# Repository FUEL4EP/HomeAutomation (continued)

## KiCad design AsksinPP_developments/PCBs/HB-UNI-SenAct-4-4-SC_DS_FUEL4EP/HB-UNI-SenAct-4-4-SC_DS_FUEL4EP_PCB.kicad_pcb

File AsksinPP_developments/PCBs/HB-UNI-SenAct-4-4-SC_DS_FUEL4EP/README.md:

# HB-UNI-SenAct-4-4-SC_DS_FUEL4EP   

**Platine für DIY AsksinPP für**
- 3x Schaltaktor für Betrieb an einem Netzfreischalter
- Akkubetrieb im Standby, automatische Ladeschaltung
- bei Aktivierung eines Aktors wird die Netzspannung zugeschaltet und am Ende wieder abgeschaltet

- geringer Standby-Verbrauch von ca. 1 mA @ 5V Vaccu, an einer weiteren Reduktion wird gearbeitet
- ein handelsübliches [4 Kanal Relais Modul](https://www.ebay.de/itm/155095219126) wird mit Distanzhaltern "huckepack" auf die Basisplatine montiert
	+ bitte darauf achten, dass das Relais-Modul den Aufdruck [P2H1588A0](./PNGs/4-Relais Modul_top_view.png) hat, da Module mit unterschiedlichen Maßen im Handel verfügbar sind.
	+ die Außenmaße des Relais-Moduls sollten 72,2 mm x 52 mm betragen
- ein STL-Modell eines 3D-druckbaren Gehäuses wird mitgeliefert, die Außenmaße des gedruckten Gehäuses sind 20,8 cm (Breite) x 13,3 cm (Tiefe) x 6,8 cm /(Höhe).
- 3x Einbausteckdosen 45 mm x 45 mm, z.B. DELOCK 81321 Easy 45 Schutzkontakt-Steckdose, werden an der Rückseite des Gehäuses angebracht
- **diese Schaltung und Platine darf ausschließlich von ausgebildeten elektrischen Fachkräften verwendet werden, siehe Disclaimer unten!**
- als passende Sketche stehen zur Verfügung:
	+ [HB-UNI-SenAct-4-4-SC_DS.ino](../../sketches/HB-UNI-SenAct-4-4-SC_DS/)
		* Abfrage der Gerätetasten durch 'Polling'
	+ [HB-UNI-SenAct-4-4-RC_DS.ino](../../sketches/HB-UNI-SenAct-4-4-RC_DS/)
		* Gerätetasten lösen einen Interrupt aus
	- Fragen und Rückmeldungen per PN bei [FUEL4EP](https://homematic-forum.de/forum/ucp.php?i=pm&mode=compose&u=20685) im Homematic Forum nachfragen.
- die Platine V1.5 behebt Fehler, die bei der Validierung eines Prototypen festgestellt und korrigiert wurden. Bitte **keine** Platinen der Versionen V1.0 bis V1.4 verwenden.
- ein passendes 3D-druckbares Gehäuse ist im STL Format und openSCAD Format [hier](./3D_Printer/case/) zu finden

	+ ein 3D Druck wurde damit erfolgreich durchgeführt, ein Prototyp ist erfolgreich aufgebaut und weitgehend validiert worden, siehe entsprechende Bilder im Verzeichnis [PNGs](./PNGs)
- **wichtige Aufbauhinweise:**
- die Materiallisten sind unter [BOM](./BOM) zu finden
    + zuerst die Niederspannungsplatine HB-UNI-SenAct-4-4-SC_DS_FUEL4EP_PCB Schritt für Schritt aufbauen, in Betrieb nehmen und testen:
	    * der Schaltplan der Platine ist [hier](./schematics/HB-UNI-SenAct-4-4-SC_DS_FUEL4EP_PCB.pdf) oder in der bereitgestellten KiCAD-Datenbasis
        + für den Arduino Pro Mini und den CC1101 Tranceiver **vor Einbau** in einem externen Testbed den Ruhestrom prüfen (<10uA) und einen Frequenztest durchführen!
        + das 'Huckepack'-4-Kanal-Relaismodul noch nicht anbringen
    - die Ausgangsspannung des Aufwärtsreglers HW-668 **vor dem Einbau** auf 7,3 Volt einstellen. Dabei eine Eingangsspannung von 5 Volt verwenden.
    - das Schaltnetzteil TIW 06-105 mit dem [3D gedruckten Stift im Gehäuseunterteil fixieren](./PNGs/internal_3.png). Vorher die Netzanschlussleitung des Schaltnetzteils auf die benötigte Länge kürzen und abisolieren.
    - das [4-fach AA Batteriefach](https://www.amazon.de/Batteriehalter-Mignon-Akkuhalter-Batteriefach-Schalter-4x-AA/dp/B0761TSC32?th=1) **unbedingt** mit dem Schalter nach [unten](./PNGs/internal_1.png) in das vorgesehene Fach platzieren, sonst werden die Anschlussdrähte beschädigt und es droht ein Kurzschluss der Akkus!
    + die 230V Schaltungsteile erst dann anschließen, wenn der Rest vollständig geprüft wurde und die Software alle notwendigen Funktionen zeigt.
        * als Erstes dann das 'Huckepack'-4-Kanal-Relaismodul anbringen und nur die Steuersignale verbinden, noch keine 230V Spannungen an den Relaisausgängen anschließen
        * dann die Funktion testen
        * falls manche LEDs (z.B. orange, blau oder pinke LEDs) zu hell im Vergleich zu den anderen LEDs leuchten sollten, bitte einen größeren Vorwiderstand wählen, z.B. 4.7 kOhm. Der vergrößerte Vorwiderstand kann auch in die 'fliegende' Vorverdrahtung der Gehäusevorderwand eingelötet werden.
        * pinke LED benötigen einen ca. 10kOhm Vorwiderstand
        * blaue LEDs benötigen einen ca. 4,7kOhm Vorwiderstand
        * erst als Letztes die 230V Verdrahtung mit der gebotenen Vorsicht anbringen
        * den Nullleiter innerhalb des Gehäuses mit einer 5-fach Wago-Klemme WAGO 221-415 (Reichelt) aus fünf Segmenten herstellen, die zwischen Platine und den Einbausteckdosen platziert wird.
        * bitte nicht vergessen, eine Sicherung einzuschrauben
        * alle Netzleitungen mit 1,5 mm2 Leitungen durchführen
        * alle Netzverbindungen spannungsfrei mit einem Ohmmeter auf Korrektheit und Niederohmigkeit prüfen
        * alle Schrauben, vor allem die an den Einbausteckdosen und an den Relaiskontakten, fest anziehen. Nach erfolgtem Aufbau nochmals auf Festigkeit prüfen.
        * die Anschlüsse an die Kaltgerätebuchse löten
        * Einbausteckdosen und Kaltgerätebuchse in die Gehäuserückwand einkleben
        * bitte darauf achten, dass Nullleiter und Phase entsprechend des [Schaltplans](./schematics/HB-UNI-SenAct-4-4-SC_DS_FUEL4EP_case.pdf) angeschlossen werden. Die Phase muss jeweils mit den Relais geschaltet werden. Bitte den Stecker des Kaltgerätekabels so in die Steckdose stecken, dass diese Zuordnung erhalten bleibt. 
        * sollte die blaue LED D1 bei Dunkelheit periodisch leicht glimmen, dann bitte einen 0,5W 220kOhm Widerstand, wie im [Schaltplan](./schematics/HB-UNI-SenAct-4-4-SC_DS_FUEL4EP_case.pdf) des Gehäuses angegeben, einlöten.
        * sollte die blaue LED D1 bei Dunkelheit dauerhaft glimmen, dann bitte einen 0,22uF 250V K X2 Kondensator die blaue LED D1 bei Dunkelheit. Es darf nur ein für 250V geeigneter Entstörkondensator verwendet werden!
        * gegebenenfalls Zugentlastungen für das Netzkabel anbringen!

## Versionen
- KiCad Schaltplan-Editor Version: 8.0.5-8.0.5-0~ubuntu22.04.1, release build unter Kubuntu22.04.1
- KiCad Leiterplatteneditor Version: 8.0.5-8.0.5-0~ubuntu22.04.1, release build unter Kubuntu22.04.1
- PCB Version 1.7 (Migration auf KiCAD 8 am 01. Okt 2024)
- Schematics  1.5 (Migration auf KiCAD 8 am 01. Okt 2024)

## Wichtige Sicherheitshinweise

- bitte die maximale Strombelastbarkeit der Relais beachten, siehe Aufdruck:

- auch bei rein ohmschen Lasten sollte die maximale Strombelastbarkeit der Relais nicht ausgereizt werden.
- bei induktiven Lastanteilen sollte weniger als die Hälfte des spezifizierten Maximalstroms zugrunde gelegt werden.  Bitte lesen Sie dazu das Datenblatt des Relais oder fragen Sie Ihre Elektrofachkraft.
- während einer längeren Abwesenheit sollte der Netzstecker der Geräts gezogen werden
- die Schaltsignale für die Relais sind **nicht** verschlüsselt. Daher bitte eine Lasten anschließen, die eventuell einen Brand auslösen könnten.
- sollte die Homematic/RaspberryMatic-Zentrale  vom Internet aus erreichbar sein, darf dieser Schalter nicht eingesetzt werden! Für die Sicherheit ist der Nutzer alleine verantwortlich!
- die automatische Ladeschaltung ist zur Zeit noch nicht in Software implementiert! Der Nutzer ist für den korrekten Ladezustand der Akkus verantwortlich.
- ein automatische Ladeschaltung wird in Zukunft als Update zur Verfügung gestellt werden. Das kann aber noch eine Weile dauern ..
- der Schalter funktioniert nun seit über einem Jahr auch ohne automatische Ladesoftware bei täglicher Nutzung: Stand Oktober 2024. Das 15 minütige Nachladen beim Einschalten reicht aus, um die Akkus ausreichend geladden zu halten.

## Fernsteuerung der Aktorkanäle mit Apple iPAD

- das Ein- und Ausschalten von Lasten kann z.B. mit Kurzbefehlen (ShortCuts) auf einem Apple iPAD gesteuert werden, siehe [hier](./control_by_iPAD_shortcuts)

## Disclaimer

- aufgrund der im Gerät frei geführten Netzspannung und des Netzspannungsanschlusses darf die Installation nur von Fachkräften durchgeführt werden, die aufgrund ihrer Ausbildung dazu befugt sind.
- die einschlägigen Sicherheits- und VDE-Bestimmungen sind unbedingt zu beachten. Durch eine unsachgemäße Installation können Sach- und Personenschäden verursacht werden, für die der Errichter haftet.
- Installationsarbeiten sowohl am primärseitigen Netzanschluss als auch am Sekundäranschluss dürfen nur **im stromlosen Zustand erfolgen. Dabei sind alle einschlägigen Vorschriften des Installationshandwerks zu beachten!** 
- alle 230 V Spannung führenden Leitungen und Lötanschlüsse sind im spannungslosen Zustand fachgerecht mit Isolationsband vor Berührungen zu schützen
- die Nutzung der hier veröffentlichten Inhalte erfolgt vollständig auf eigenes Risiko und ohne jede Gewähr

## Lizenz 

**Creative Commons BY-NC-SA**<br>
Give Credit, NonCommercial, ShareAlike

<br />This work is licensed under a <a rel="license" href="http://creativecommons.org/licenses/by-nc-sa/4.0/">Creative Commons Attribution-NonCommercial-ShareAlike 4.0 International License</a>.

-EOF

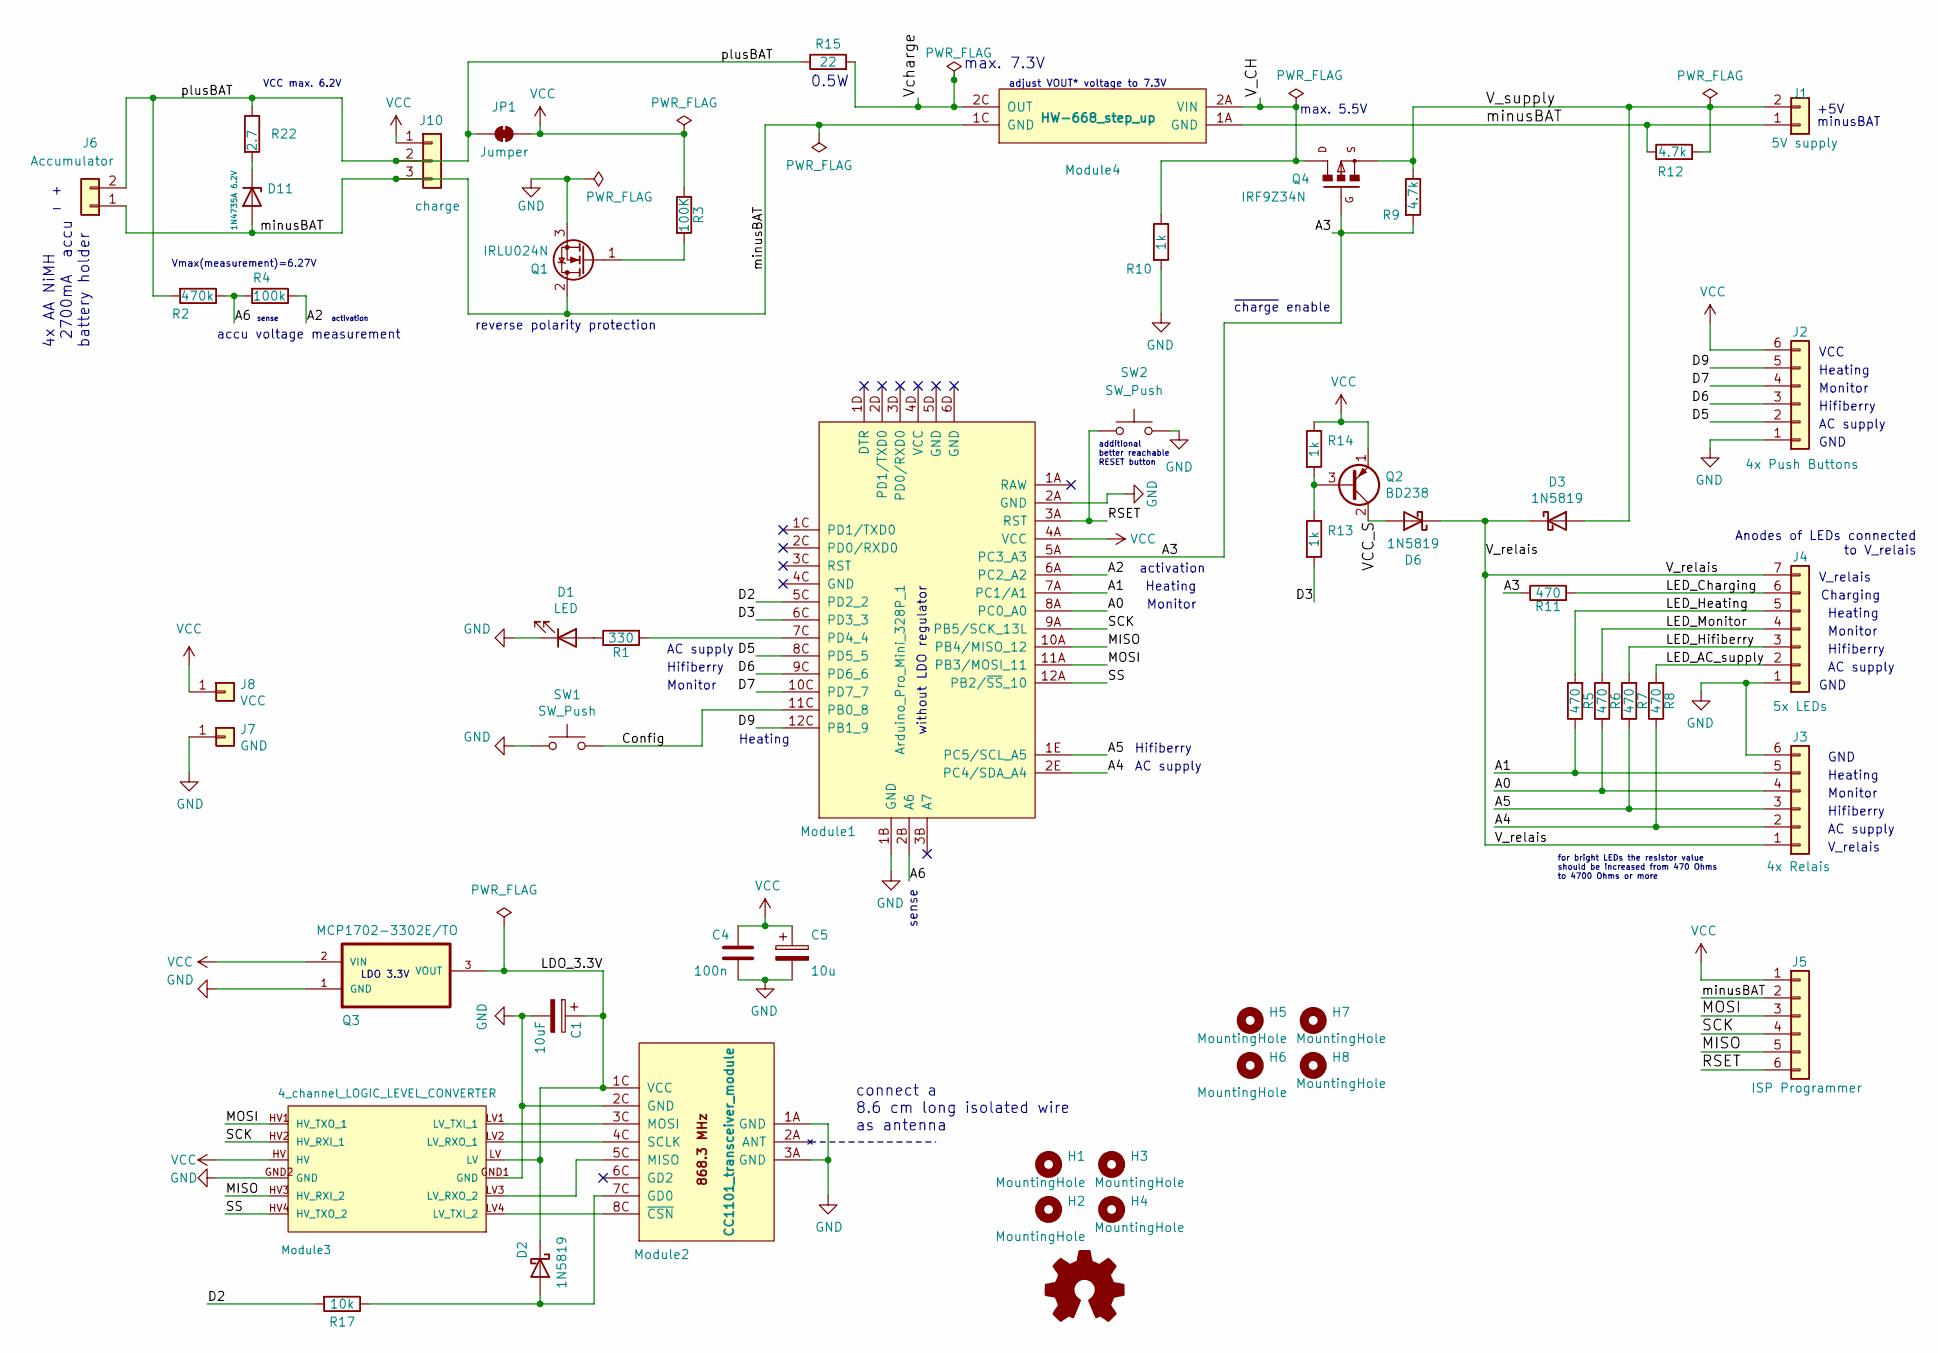
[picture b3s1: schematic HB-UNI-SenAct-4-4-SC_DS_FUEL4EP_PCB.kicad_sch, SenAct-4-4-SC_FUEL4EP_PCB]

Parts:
C1: 10uF; CP_Radial_D5.0mm_P2.50mm
C4: 100n; C_Disc_D7.5mm_W2.5mm_P5.00mm
C5: 10u; CP_Radial_D5.0mm_P2.00mm
D1: LED; LED_D3.0mm
D2, D3, D6: 1N5819; D_DO-41_SOD81_P7.62mm_Horizontal
D11: 1N4735A 6.2V; D_DO-41_SOD81_P7.62mm_Horizontal
H1, H2, H3, H4, H5, H6, H7, H8: MountingHole; MountingHole_M3
J1: 5V supply; PinHeader_1x02_P2.54mm_Vertical
J2: 4x Push Buttons; PinHeader_1x06_P2.54mm_Vertical
J3: 4x Relais; PinHeader_1x06_P2.54mm_Vertical
J4: 5x LEDs; PinHeader_1x07_P2.54mm_Vertical
J5: ISP Programmer; PinHeader_1x06_P2.54mm_Vertical
J6: Accumulator; PinHeader_1x02_P2.54mm_Vertical
J7: GND; PinHeader_1x01_P1.27mm_Vertical
J8: VCC; PinHeader_1x01_P1.27mm_Vertical
J10: charge; PinHeader_1x03_P2.54mm_Vertical
JP1: Jumper; SolderJumper-2_P1.3mm_Bridged2Bar_Pad1.0x1.5mm
LOGO1: Logo_Open_Hardware_Small; CC-BY-ND-SA
Module1: Arduino_Pro_Mini_328P_1; ArduinoProMini
Module2: CC1101_transceiver_module; CC1101
Module3: 4_channel_LOGIC_LEVEL_CONVERTER
Module4: HW-668_step_up; HW-668_step-up
Q1: IRLU024N; TO-251-3_Vertical
Q2: BD238; TO-126-3_Vertical
Q3: MCP1702-3302E/TO; TO127P254X533-3
Q4: IRF9Z34N; TO220V
R1: 330; R_Axial_DIN0204_L3.6mm_D1.6mm_P5.08mm_Horizontal
R2: 470k; R_Axial_DIN0207_L6.3mm_D2.5mm_P10.16mm_Horizontal
R3: 100K; R_Axial_DIN0204_L3.6mm_D1.6mm_P5.08mm_Horizontal
R4: 100k; R_Axial_DIN0207_L6.3mm_D2.5mm_P10.16mm_Horizontal
R5, R6, R7, R8, R11: 470; R_Axial_DIN0204_L3.6mm_D1.6mm_P5.08mm_Horizontal
R9, R12: 4.7k; R_Axial_DIN0204_L3.6mm_D1.6mm_P5.08mm_Horizontal
R10, R13, R14: 1k; R_Axial_DIN0204_L3.6mm_D1.6mm_P5.08mm_Horizontal
R15: 22; R_Axial_DIN0309_L9.0mm_D3.2mm_P20.32mm_Horizontal
R17: 10k; R_Axial_DIN0204_L3.6mm_D1.6mm_P5.08mm_Horizontal
R22: 2.7; R_Axial_DIN0309_L9.0mm_D3.2mm_P20.32mm_Horizontal
SW1, SW2: SW_Push; SW_PUSH_6mm_H4.3mm

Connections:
/A0: J3.4, Module1.8A (PC0_A0), R6.1
/A1: J3.5, Module1.7A (PC1/A1), R5.1
/A2: Module1.6A (PC2_A2), R4.1
/A3: Module1.5A (PC3_A3), Q4.1, R9.2, R11.1
/A4: J3.2, Module1.2E (PC4/SDA_A4), R8.1
/A5: J3.3, Module1.1E (PC5/SCL_A5), R7.1
/A6: Module1.2B (A6), R2.1, R4.2
/Config: Module1.11C (PB0_8), SW1.2
/D2: Module1.5C (PD2_2), R17.2
/D3: Module1.6C (PD3_3), R13.2
/D5: J2.2, Module1.8C (PD5_5)
/D6: J2.3, Module1.9C (PD6_6)
/D7: J2.4, Module1.10C (PD7_7)
/D9: J2.5, Module1.12C (PB1_9)
/LDO_3.3V: C1.1, D2.1 (K), Module2.1C (VCC), Module3.LV, Q3.3 (VOUT)
/LED_AC_supply: J4.2, R8.2
/LED_Charging: J4.6, R11.2
/LED_Heating: J4.5, R5.2
/LED_Hifiberry: J4.3, R7.2
/LED_Monitor: J4.4, R6.2
/MISO: J5.5, Module1.10A (PB4/MISO_12), Module3.HV3 (HV_RXI_2)
/MOSI: J5.3, Module1.11A (PB3/MOSI_11), Module3.HV1 (HV_TXO_1)
/RSET: J5.6, Module1.3A (RST), SW2.1
/SCK: J5.4, Module1.9A (PB5/SCK_13L), Module3.HV2 (HV_RXI_1)
/SS: Module1.12A (PB2/~SS_10), Module3.HV4 (HV_TXO_2)
/VCC_S: D6.2 (A), Q2.2 (C)
/V_CH: Module4.2A (VIN), Q4.2, R10.1
/V_relais: D3.1 (K), D6.1 (K), J3.1, J4.7
/V_supply: D3.2 (A), J1.2, Q4.3, R9.1, R12.2
/Vcharge: Module4.2C (OUT), R15.2
/minusBAT: D11.2 (A), J1.1, J5.2, J6.1, J10.3, Module4.1A (GND), Module4.1C (GND), Q1.2 (D), R12.1
/plusBAT: J6.2, J10.2, JP1.1 (A), R2.2, R15.1, R22.1
GND: C1.2, C4.2, C5.2, D1.1 (K), J2.1, J3.6, J4.1, J7.1, Module1.1B (GND), Module1.2A (GND), Module2.1A (GND), Module2.2C (GND), Module2.3A (GND), Module3.GND1 (GND), Module3.GND2 (GND), Q1.3 (S), Q3.1 (GND), R10.2, SW1.1, SW2.2
unnamed: D1.2 (A), R1.1
unnamed: D2.2 (A), Module2.7C (GD0), R17.1
unnamed: D11.1 (K), R22.2
unnamed: Module1.7C (PD4_4), R1.2
unnamed: Module2.5C (MISO), Module3.LV3 (LV_RXO_2)
unnamed: Module2.3C (MOSI), Module3.LV1 (LV_TXI_1)
unnamed: Module2.4C (SCLK), Module3.LV2 (LV_RXO_1)
unnamed: Module2.8C (~CSN), Module3.LV4 (LV_TXI_2)
unnamed: Q1.1 (G), R3.2
unnamed: Q2.3 (B), R13.1, R14.2
VCC: C4.1, C5.1, J2.6, J5.1, J8.1, J10.1, JP1.2 (B), Module1.4A (VCC), Module3.HV, Q2.1 (E), Q3.2 (VIN), R3.1, R14.1

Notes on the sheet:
Monitor
Heating
sense
Charging
AC supply
Hifiberry
reverse polarity protection
for bright LEDs the resistor value should be increased from 470 Ohms to 4700 Ohms or more
activation
connect a 8.6 cm long isolated wire as antenna
LDO 3.3V
without LDO regulator
0.5W
adjust VOUT* voltage to 7.3V
additional better reachable RESET button
accu voltage measurement
4x AA NiMH 2700mA accu battery holder
V_relais
VCC max. 6.2V
~{charge} enable
minusBAT
VCC
GND
max. 5.5V
Anodes of LEDs connected to V_relais
Vmax(measurement)=6.27V
max. 7.3V
+5V

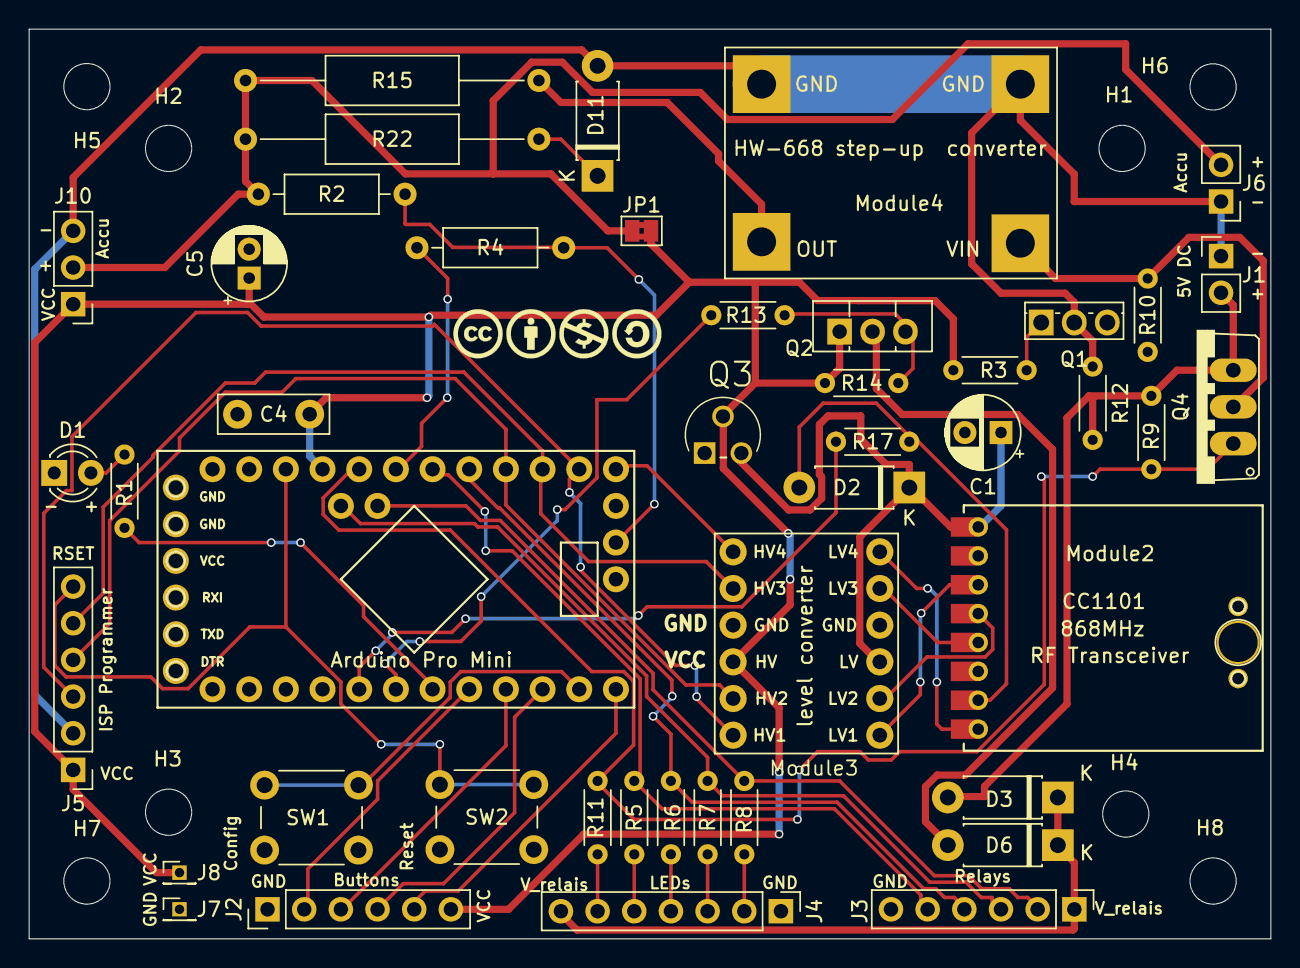
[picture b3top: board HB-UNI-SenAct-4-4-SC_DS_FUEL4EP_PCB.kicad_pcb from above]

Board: 2 copper layers, 86.0 x 63.0 mm, 54 parts (0 on the bottom side), 44 nets.

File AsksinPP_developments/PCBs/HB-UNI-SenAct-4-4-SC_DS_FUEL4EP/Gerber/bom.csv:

Designator,Footprint,Quantity,Value,LCSC Part #
C1,CP_Radial_D5.0mm_P2.50mm,1,10uF,
C4,C_Disc_D7.5mm_W2.5mm_P5.00mm,1,100n,
C5,CP_Radial_D5.0mm_P2.00mm,1,10u,
D1,LED_D3.0mm,1,LED,
D11,D_DO-41_SOD81_P7.62mm_Horizontal,1,1N4735A 6.2V,
"D2, D3, D6",D_DO-41_SOD81_P7.62mm_Horizontal,3,1N5819,
"H1, H2, H3, H4, H5, H6, H7, H8",MountingHole_M3,8,MountingHole,
J1,PinHeader_1x02_P2.54mm_Vertical,1,5V  supply,
J10,PinHeader_1x03_P2.54mm_Vertical,1,charge,
J2,PinHeader_1x06_P2.54mm_Vertical,1,4x Push Buttons,
J3,PinHeader_1x06_P2.54mm_Vertical,1,4x Relais,
J4,PinHeader_1x07_P2.54mm_Vertical,1,5x LEDs,
J5,PinHeader_1x06_P2.54mm_Vertical,1,ISP Programmer,
J6,PinHeader_1x02_P2.54mm_Vertical,1,Accumulator,
J7,PinHeader_1x01_P1.27mm_Vertical,1,GND,
J8,PinHeader_1x01_P1.27mm_Vertical,1,VCC,
JP1,SolderJumper-2_P1.3mm_Bridged2Bar_Pad1.0x1.5mm,1,Jumper,
LOGO1,CC-BY-ND-SA,1,Logo_Open_Hardware_Small,
Module1,ArduinoProMini,1,Arduino_Pro_Mini_328P_1,
Module2,CC1101,1,CC1101_transceiver_module,
Module3,4_channel_LOGIC_LEVEL_CONVERTER,1,4_channel_LOGIC_LEVEL_CONVERTER,
Module4,HW-668_step-up,1,HW-668_step-up,
Q1,TO-251-3_Vertical,1,IRLU024N,
Q2,TO-126-3_Vertical,1,BD238,
Q4,TO220V,1,IRF9Z34N,
Q5,TO127P254X533-3,1,MCP1702-2802E_TO,MCP1702-2802E/TO
R1,R_Axial_DIN0204_L3.6mm_D1.6mm_P5.08mm_Horizontal,1,330,
"R10, R13, R14",R_Axial_DIN0204_L3.6mm_D1.6mm_P5.08mm_Horizontal,3,1k,
"R11, R5, R6, R7, R8",R_Axial_DIN0204_L3.6mm_D1.6mm_P5.08mm_Horizontal,5,470,
R15,R_Axial_DIN0309_L9.0mm_D3.2mm_P20.32mm_Horizontal,1,22,
R17,R_Axial_DIN0204_L3.6mm_D1.6mm_P5.08mm_Horizontal,1,10k,
R2,R_Axial_DIN0207_L6.3mm_D2.5mm_P10.16mm_Horizontal,1,470k,
R22,R_Axial_DIN0309_L9.0mm_D3.2mm_P20.32mm_Horizontal,1,2.7,
R3,R_Axial_DIN0204_L3.6mm_D1.6mm_P5.08mm_Horizontal,1,100K,
R4,R_Axial_DIN0207_L6.3mm_D2.5mm_P10.16mm_Horizontal,1,100k,
R9,R_Axial_DIN0204_L3.6mm_D1.6mm_P5.08mm_Horizontal,1,4.7k,
"SW1, SW2",SW_PUSH_6mm_H4.3mm,2,SW_Push,

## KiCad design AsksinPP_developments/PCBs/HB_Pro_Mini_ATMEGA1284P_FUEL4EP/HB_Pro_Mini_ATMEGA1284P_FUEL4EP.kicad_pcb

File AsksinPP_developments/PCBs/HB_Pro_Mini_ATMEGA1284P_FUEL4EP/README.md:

# HB_Pro_Mini_ATMEGA1284P_FUEL4EP  

## Arduino Pro Mini Klon mit der 4-fachen Größe von Flash, SRAM und EEPROM Speicher eines ATmega1284p Prozessorbausteins verglichen mit dem Standard ATmega328p Prozessorbaustein

)

- [ATmega1284p](https://ww1.microchip.com/downloads/en/DeviceDoc/Atmel-42719-ATmega1284P_Datasheet.pdf) statt ATmega328p
- ATmega1284p im 7mmx7mm 44 Pin VQFN Gehäuse
- löst die meisten Speicherprobleme, wenn ein Sketch nicht mehr in einen ATMega328P passt:
	+ 128kByte Flash Speicher (4x vom ATmega 328p)
	+ 16KByte SRAM (4x vom ATmega 328p)
	+ 4 kByte EEPROM (4x vom ATmega 328p)
- weitere Verbesserungen gegenüber dem Standard ATMega328P basierenden Pro Mini:
	+ ein zusätzlicher UART
	+ ein zusätzlicher externer Interrupt
	+ ein zusätzlicher 16-bit Timer	
	* JTAG Schnittstelle
- optimiert für AsksinPP DIY Projekte
	+ sehr geringer Ruhestrom ohne Auslöten des Spannungsreglers und der LEDs
- abgeleitet vom Sparkfun Electronic's Arduino-Pro-Mini (Rev 14)
	+ weitgehend pinkompatibel
	+ kein Spannungsregler
	+ keine LEDs
	+ 8 MHz Resonator
- optional zusätzlicher Boost-Konverter
	+ 1,5V..5.5V Eingangsspannung auf 3,3V Versorgungsspannung
	+ [TPS61221](https://www.ti.com/lit/ds/symlink/tps61221.pdf?ts=1739637159741&ref_url=https%253A%252F%252Fwww.ti.com%252Fproduct%252Fde-de%252FTPS61221) basierend
- weitgehend pin- und softwarekompatibel zum  [Pro Mini XL 1284P V2](https://prominimicros.com/)
	+ keine LED
	+ 8 MHz Resonator statt 20 MHz Quarz
	+ 3.3V Betriebsspannung mit optionalem Boost-Konverter
	+ max. 5,5V Betriebsspannung ohne optionalem Boost-Konverter
	+ die [Anleitungen für den Pro Mini XL 1284P V2](https://prominimicros.com/) passen weitgehend auch für HB_Pro_Mini_ATMEGA1284P_FUEL4EP
- passende Arduino Bibliothek:[ATmega1284P Arduino MightyCore Bibliothek](https://github.com/MCUdude/MightyCore)

- MightyCore ATMega1284P VQFN44 Standardpinbelegung (=TQFP44)

- [hier die Pinbelegung](./PinOut/) als Tabelle

- passend zu folgenden AsksinPP Basisplatinen (wird später durch weitere Platinen ergänzt)
	* [HB-UNI-SEN-BATT_FUEL4EP](https://github.com/FUEL4EP/HomeAutomation/tree/master/AsksinPP_developments/PCBs/HB-UNI-SEN-BATT_FUEL4EP)

## Platinenmaße

- Platinengröße: 17.78 mm x 33.02 mm (0.7" x 1.3")
- Platinendicke: 1,6 mm (bei der Bestellung bei JLCPCB auswählen)

## Stromlaufplan

- ist [hier](./Schematics/HB_Pro_Mini_ATMEGA1284P_FUEL4EP.pdf)

## Status

- diese Platine wurde in der Version 1.0 bei JLCPCB erfolgreich gefertigt und assembliert:

- für die Systemvalidierung wude als Hardware verwandt:
	+ [HB-UNI-SEN-BATT_FUEL4EP V1.5](https://github.com/FUEL4EP/HomeAutomation/tree/master/AsksinPP_developments/PCBs/HB-UNI-SEN-BATT_FUEL4EP)
	+ [HB_Pro_Mini_ATMEGA1284P_FUEL4EP V1.0](https://github.com/FUEL4EP/HomeAutomation/tree/master/AsksinPP_developments/PCBs/HB_Pro_Mini_ATMEGA1284P_FUEL4EP)
	+ [I2C_Module_SHT45_BME280_small_FUEL4EP V1.5](https://github.com/FUEL4EP/HomeAutomation/tree/master/AsksinPP_developments/PCBs/I2C_Module_SHT45_BME280_small_FUEL4EP)
	+ getestet wurden folgende Spannungeversorgungen:
		* 1x AA Alkaline Batterie
		* 2x AA Alkaline Batterie
		* 1x NiMH AA Akkumulator
		* 2x NiMH AA Akkumulator
- für die Systemvalidierung wurde als Software verwendet:
	+ [HB-UNI-Sensor1-THPD-SHT45_BME280](https://github.com/FUEL4EP/HomeAutomation/tree/master/AsksinPP_developments/sketches/HB-UNI-Sensor1-THPD-SHT45_BME280)
	+ die Stromaufnahme im Schlafmodus mit 1x AA Alkaline Battterie beträgt ca. 22uA.

## Rückmeldungen

- und Verbesserungsvorschläge sind willkommen.
- PN an [FUEL4EP](https://homematic-forum.de/forum/ucp.php?i=pm&mode=compose&u=20685) im Homematic Forum oder als Github Issue

### KiCAD Plugin
- für die Erzeugung der JLCPCB Produktionsdaten wurde das Plugin [KiCAD JLCPCB tools](https://github.com/bouni/kicad-jlcpcb-tools) verwendet.

## Daten für die Bestellung bei JLCPCB

- die Daten für die Bestellung liegen im Verzeichnis [./jlcpcb/production_files/](./jlcpcb/production_files/)
- Gerber-Daten als Zip-Datei
- BOM- und CPL-Daten als CSV-Datei

## lokale Installation des Github Releases auf Deinem Computer

- gehe bitte in Dein Zielinstallationsverzeichnis, wo Du mit der HB_Pro_Mini_ATMEGA1284P_FUEL4EP Platine mit KiCAD arbeiten möchtest

  - gebe dort 'git clone https://github.com/FUEL4EP/HomeAutomation.git' ein
	  + damit lädst Du mein [Sammelrepository](https://github.com/FUEL4EP/HomeAutomation) für alle meine auf Github freigegebenen HomeBrew Entwicklungen herunter.
  - dann findest Du ein neues Verzeichnis 'HomeAutomation' auf Deinem Rechner, das alle meine auf Github freigebenen Entwicklungen enthält, siehe [README.md](https://github.com/FUEL4EP/HomeAutomation/blob/master/README.md)
  	+ mache bitte regelmäßig ein Update mit 'git pull'
 -	die Platine HB_Pro_Mini_ATMEGA1284P_FUEL4EP findest Du unter './HomeAutomation/tree/master/AsksinPP_developments/PCBs/HB_Pro_Mini_ATMEGA1284P_FUEL4EP'
 
- alternativ kann vom Github [Sammelrepository](https://github.com/FUEL4EP/HomeAutomation) die ZIP-Datei HomeAutomation-master.zip heruntergeladen und auf dem lokalen Rechner ausgepackt werden. Bitte dann regelmäßig auf Github nach Updates schauen.

### Hinweise
* Achtung: Kein Überspannungsschutz oder Verpolungsschutz vorhanden
* bei der Nutzung des JLCPCB SMT Bestückungsservice ist darauf zu achten, dass **alle** benötigten SMD Bauteile als im Lager **verfügbar** angezeigt werden. Sonst bitte **NICHT** bestellen!

### KiCAD Plugin
- für die Erzeugung der JLCPCB Produktionsdaten wurde das Plugin [KiCAD JLCPCB tools](https://github.com/bouni/kicad-jlcpcb-tools) verwendet.

## Bestellen von Platinen

- die Platine kann direkt bei JLCPCB bestellt und dort auch assembliert werden
- die notwendigen Produktionsdaten stehen [hier](./jlcpcb/production_files/)
- die folgenden Bauteile müssen [vorab bei JLCPCB bestellt werden](https://jlcpcb.com/help/article/53-what-is-jlcpcb-parts-pre-order-service):
	+ [TI TPS61221DCKT](https://jlcpcb.com/partdetail/TexasInstruments-TPS61221DCKT/C2865756) 
	+ [Murata LQH3NPN4R7MMEL 4.7 uH SMD Induktivität](https://jlcpcb.com/partdetail/MurataElectronics-LQH3NPN4R7MMEL/C576538)
	+ [Panasonic EVPBB0AAB000 Tactile Switch SPST-NO Top Actuated Surface Mount](https://jlcpcb.com/partdetail/Panasonic-EVPBB0AAB000/C558803)
	+ [Murata CSTNE8M00GH5L000R0 8MHz 33pF 40Ω SMD3213-3P Ceramic Resonators ROHS](https://jlcpcb.com/partdetail/946709-CSTNE8M00GH5L000R0/C882602)
- bei der Nutzung des JLCPCB SMT Bestückungsservice ist darauf zu achten, dass **alle** benötigten SMD Bauteile als im Lager **verfügbar** angezeigt werden. Sonst bitte **NICHT** bestellen!

## Sammelbestellung

- wer Interesse an einer gemeinsamen Bestellung von Platinen und/oder Gehäusen bei JLCPCB hat, fragt bitte per per PN bei bei [FUEL4EP](https://homematic-forum.de/forum/ucp.php?i=pm&mode=compose&u=20685) an.
- wenn genügend Interesse (>= 20 bestückte Platinen und/oder 3D gedruckten Gehäusen) zustande kommt, biete ich an, Platinen  und Gehäuse bei JLCPCB zu bestellen und gegen Vorkasse per PayPal zum Selbstkostenpreis + Versandkosten innerhalb Deutschland + 3 Euro Aufwandspauschale pro Versand weiterzuverkaufen. Vor einer Bestellung wird ein Angebot bei JLCPCB eingeholt und an die Interessenten zur Zustimmung verteilt.
- je mehr sich an einer Sammelbestellung beteiligen, desto geringer werden die einmaligen Kosten wie Rüstkosten, Versand, etc.

## Versionsverlauf

-   V1.0 15. Feb 2025: Initiale Veröffentlichung auf Github
- KiCad Schaltplan-Editor Version: 8.0.8-8.0.8-0~ubuntu22.04.1, release build unter Kubuntu22.04.4
- KiCad Leiterplatteneditor Version: 8.0.8-8.0.8-0~ubuntu22.04.1, release build unter Kubuntu22.04.4
- PCB Version 1.0
- Schematics  1.0

## Disclaimer

-   die Nutzung der hier veröffentlichten Inhalte erfolgt vollständig auf eigenes Risiko und ohne jede Gewähr.

## Lizenz 

**Creative Commons BY-NC-SA**<br>
Give Credit, NonCommercial, ShareAlike

<br />This work is licensed under a <a rel="license" href="http://creativecommons.org/licenses/by-nc-sa/4.0/">Creative Commons Attribution-NonCommercial-ShareAlike 4.0 International License</a>.

-EOF

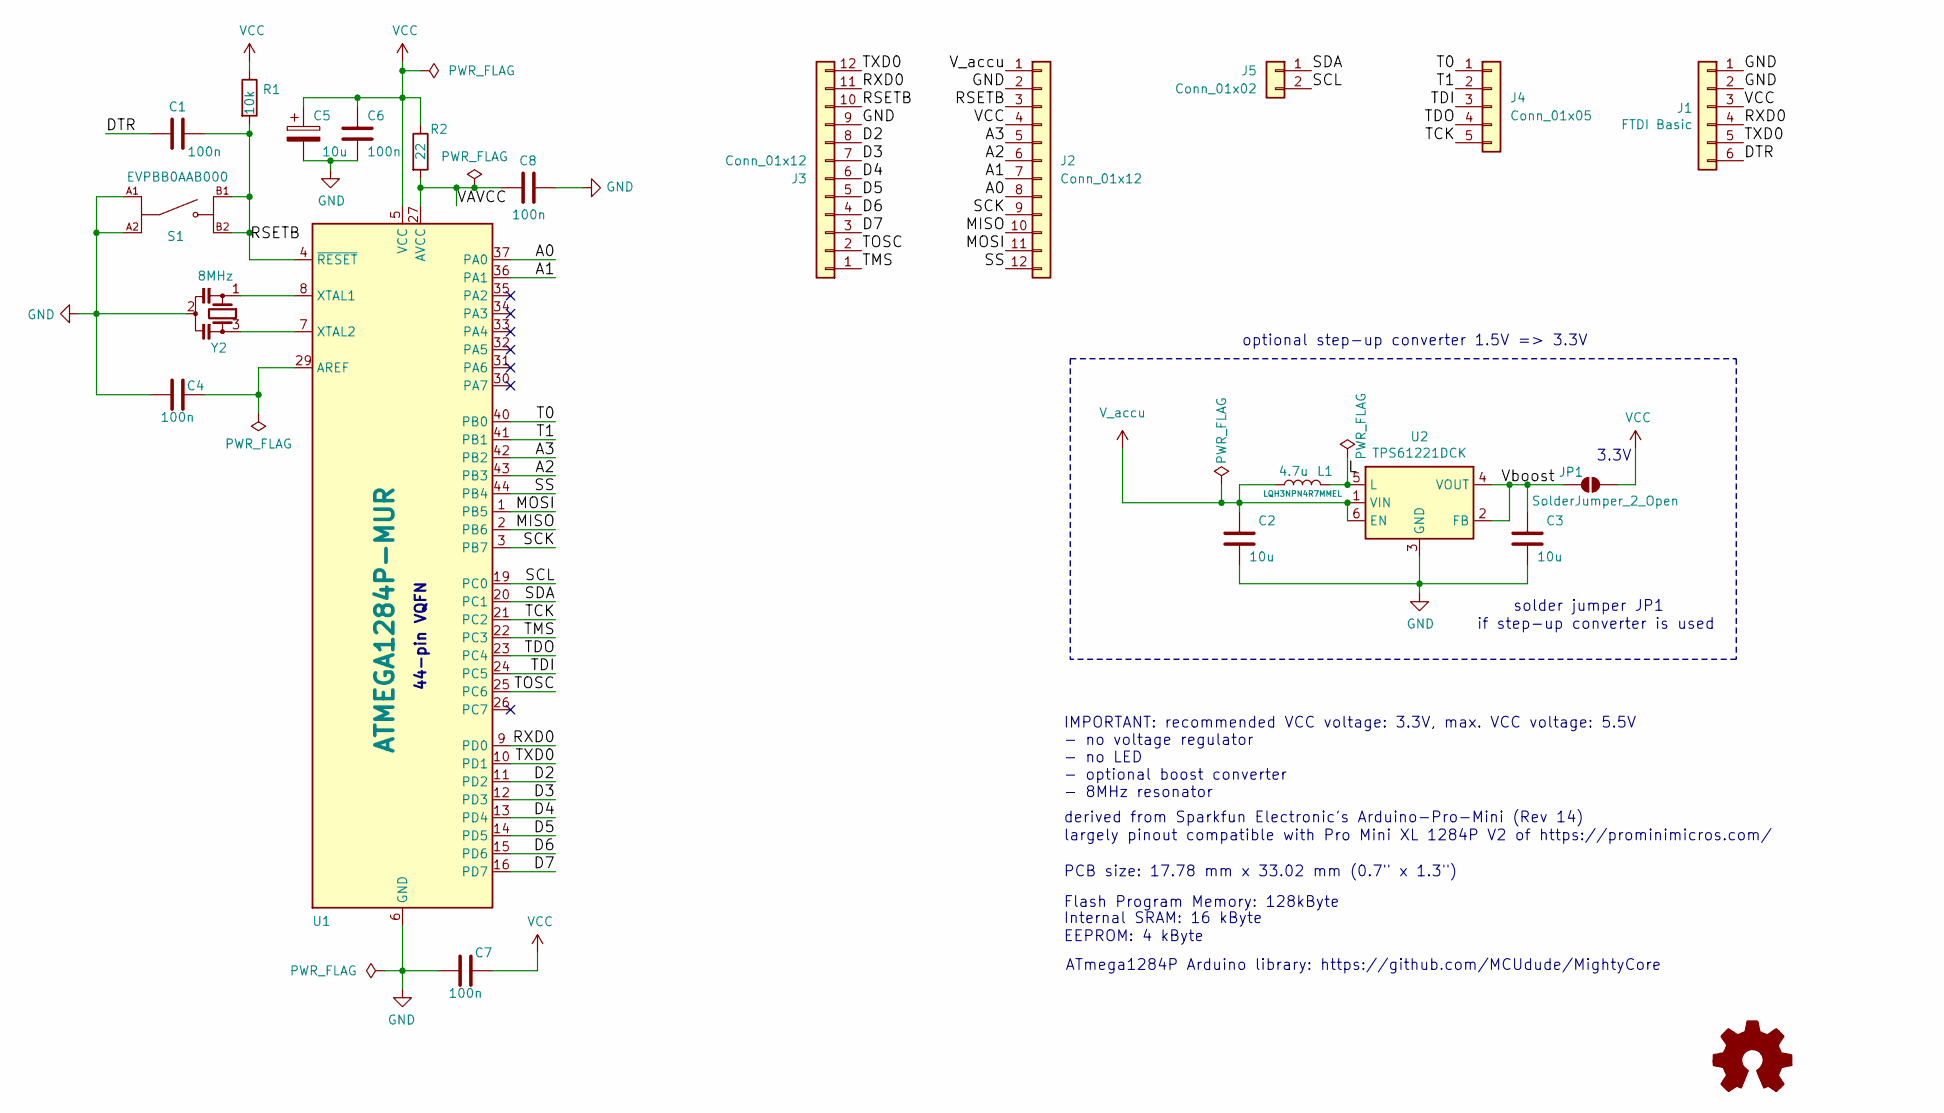
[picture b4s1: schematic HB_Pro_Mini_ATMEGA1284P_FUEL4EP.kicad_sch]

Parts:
C1, C4, C6, C7, C8: 100n; C_0402_1005Metric; LCSC C1525
C2, C3: 10u; C_0805_2012Metric; LCSC C15850
C5: 10u; C_0402_1005Metric; LCSC C15525
J1: FTDI Basic; PinHeader_1x06_P2.54mm_Vertical_FUEL4EP
J2, J3: Conn_01x12; PinHeader_1x12_P2.54mm_Vertical_FUEL4EP
J4: Conn_01x05; PinHeader_1x05_P2.54mm_Vertical_FUEL4EP
J5: Conn_01x02; PinHeader_1x02_P2.54mm_Vertical_FUEL4EP
JP1: SolderJumper_2_Open; SolderJumper-2_P1.3mm_Open_Pad1.0x1.5mm
L1: 4.7u; FUEL4EP_Inductor_SMD_1; LCSC C576538
LOGO1: Logo_Open_Hardware_Small; CC-BY-ND-SA
R1: 10k; R_0402_1005Metric; LCSC C25744
R2: 22; R_0402_1005Metric; LCSC C25092
S1: EVPBB0AAB000; SW_EVPBB0AAB000; LCSC C558803
U1: ATMEGA1284P-MUR; QFN-44-1EP_7x7mm_P0.5mm_EP5.15x5.15mm_ThermalVias; LCSC C2053632
U2: TPS61221DCK; Texas_R-PDSO-G6; LCSC C2865756
Y2: 8MHz; Resonator_SMD_Murata_CSTxExxV-3Pin_3.0x1.1mm; LCSC C882602

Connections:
/A0: J2.8, U1.37 (PA0)
/A1: J2.7, U1.36 (PA1)
/A2: J2.6, U1.43 (PB3)
/A3: J2.5, U1.42 (PB2)
/D2: J3.8, U1.11 (PD2)
/D3: J3.7, U1.12 (PD3)
/D4: J3.6, U1.13 (PD4)
/D5: J3.5, U1.14 (PD5)
/D6: J3.4, U1.15 (PD6)
/D7: J3.3, U1.16 (PD7)
/DTR: C1.2, J1.6
/L: L1.2, U2.5 (L)
/MISO: J2.10, U1.2 (PB6)
/MOSI: J2.11, U1.1 (PB5)
/RSETB: C1.1, J2.3, J3.10, R1.2, S1.B1, S1.B2, U1.4 (~RESET)
/RXD0: J1.4, J3.11, U1.9 (PD0)
/SCK: J2.9, U1.3 (PB7)
/SCL: J5.2, U1.19 (PC0)
/SDA: J5.1, U1.20 (PC1)
/SS: J2.12, U1.44 (PB4)
/T0: J4.1, U1.40 (PB0)
/T1: J4.2, U1.41 (PB1)
/TCK: J4.5, U1.21 (PC2)
/TDI: J4.3, U1.24 (PC5)
/TDO: J4.4, U1.23 (PC4)
/TMS: J3.1, U1.22 (PC3)
/TOSC: J3.2, U1.25 (PC6)
/TXD0: J1.5, J3.12, U1.10 (PD1)
/VAVCC: C8.2, R2.2, U1.27 (AVCC)
/Vboost: C3.1, JP1.2 (B), U2.2 (FB), U2.4 (VOUT)
GND: C2.2, C3.2, C4.2, C5.2, C6.2, C7.2, C8.1, J1.1, J1.2, J2.2, J3.9, S1.A1, S1.A2, U1.6 (GND), U1.18 (GND), U1.28 (GND), U1.39 (GND), U1.45 (GND), U2.3 (GND), Y2.2
unnamed: C4.1, U1.29 (AREF)
unnamed: U1.8 (XTAL1), Y2.1
unnamed: U1.7 (XTAL2), Y2.3
VCC: C5.1, C6.1, C7.1, J1.3, J2.4, JP1.1 (A), R1.1, R2.1, U1.5 (VCC), U1.17 (VCC), U1.38 (VCC)
V_accu: C2.1, J2.1, L1.1, U2.1 (VIN), U2.6 (EN)

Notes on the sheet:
ATmega1284P Arduino library: https://github.com/MCUdude/MightyCore
derived from Sparkfun Electronic's Arduino-Pro-Mini (Rev 14)
PCB size: 17.78 mm x 33.02 mm (0.7" x 1.3")
3.3V
if step-up converter is used
optional step-up converter 1.5V => 3.3V
44-pin VQFN
EEPROM: 4 kByte
Flash Program Memory: 128kByte
largely pinout compatible with Pro Mini XL 1284P V2 of https://prominimicros.com/
Internal SRAM: 16 kByte
solder jumper JP1
IMPORTANT: recommended VCC voltage: 3.3V, max. VCC voltage: 5.5V - no voltage regulator - no LED - optional boost converter - 8MHz resonator

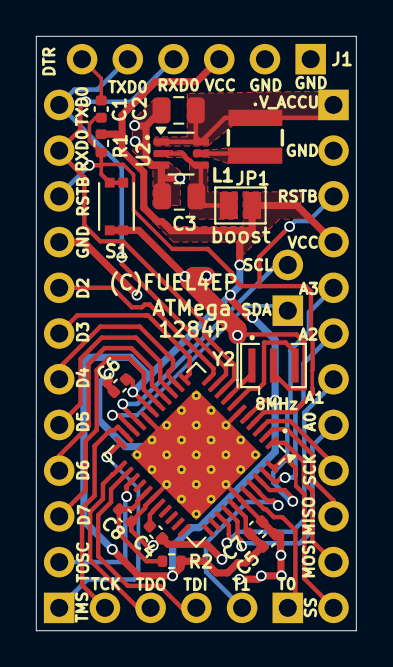
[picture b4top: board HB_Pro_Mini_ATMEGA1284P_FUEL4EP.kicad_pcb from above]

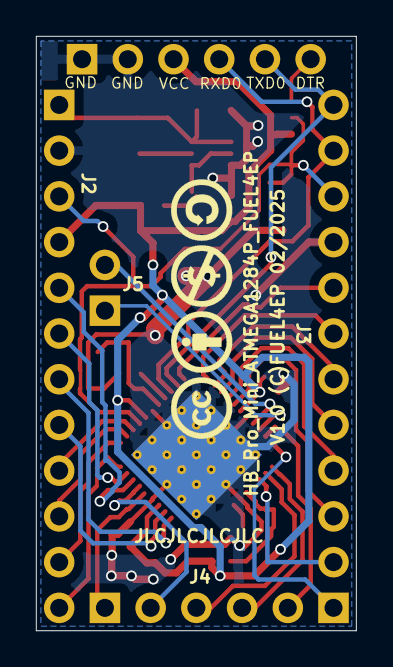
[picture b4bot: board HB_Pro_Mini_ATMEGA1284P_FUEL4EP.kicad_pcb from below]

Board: 2 copper layers, 17.8 x 33.0 mm, 22 parts (5 on the bottom side), 36 nets.

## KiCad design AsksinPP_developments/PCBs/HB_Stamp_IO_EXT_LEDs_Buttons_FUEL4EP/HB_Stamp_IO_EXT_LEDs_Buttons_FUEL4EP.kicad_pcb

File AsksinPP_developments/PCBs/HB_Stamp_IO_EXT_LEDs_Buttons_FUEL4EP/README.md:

# HB_Stamp_IO_EXT_LEDs_Buttons_FUEL4EP  

**kleine DIY AsksinPP Signalisierungs- und Eingabeaufsteckplatine**
- passende Aufsteckplatine für [HB_Stamp_IO_ATMega1284P_FUEL4EP](https://github.com/FUEL4EP/HomeAutomation/tree/master/AsksinPP_developments/PCBs/HB_Stamp_IO_ATMega1284P_FUEL4EP)
- für die Eingabe- und Signalisierung von 4 Heimautomatisierungszuständen
- Platinenmaße 22 mm x 27 mm
- 4x 3mm Signalisierungs-LEDs
- 4x Eingabetaster
- 1x optionaler Piezosignalgeber auf der Platinenrückseite
-

## Credits

- mein besonderer Dank geht an papa für [AsksinPP](https://github.com/pa-pa/AskSinPP) und [Jérôme jp112sdl](https://github.com/jp112sdl) für die stete Unterstützung.

## Status

- ein Prototyp der Platine V1.0 wurde bei JLCPCB gefertigt. Der zugehörige AsksinPP-Sketch ist in Entwicklung

## Eigenschaften

- kompletter Datensatz für KiCAD 8 auf Github verfügbar:
    + 'git clone https://github.com/FUEL4EP/HomeAutomation.git' oder als [ZIP-Datei](https://github.com/FUEL4EP/HomeAutomation/archive/refs/heads/master.zip)
    + die Platinendaten sind dann unter 'HomeAutomation/AsksinPP_developments/PCBs/HB_Stamp_IO_EXT_LEDs_Buttons_FUEL4EP' direkt mit KiCAD aufrufbar
- neue Eigenschaften:
    + SMD Bestückung, wo möglich
    + alle SMD Bausteine sind mit dem JLCPCB SMT Bestückungsservice kostengünstig und qualitativ hochwertig bestückbar
    + JLCPCB BOM and CPL Dateien für SMT Service werden [bereitgestellt](./jlcpcb/production_files)
    + die AsksinPP Reset- und Config-Taster sind aus Platzgründen als Platinenjumper ausgeführt. Bitte geeignet kurz überbrücken, z.B. mit einem Schraubendreher

### Passende AsksinPP Projekte von FUEL4EP
   + in Entwicklung, werden abgeleitet aus [HM-LC-SWX-SM](https://github.com/pa-pa/AskSinPP/tree/master/examples/HM-LC-SWX-SM) und [HM-LC-SW1-BA-PCB](https://github.com/pa-pa/AskSinPP/tree/master/examples/HM-LC-SW1-BA-PCB)
   + Akkubetrieb ähnlich [HB-UNI-Sensor1-THPD-SHT45_BME280](https://github.com/FUEL4EP/HomeAutomation/tree/master/AsksinPP_developments/sketches/HB-UNI-Sensor1-THPD-SHT45_BME280)
   + eingeschaltete LEDs blinken alle 10 Sekunden nur sehr kurz
   + optionaler Piezosignalgeber zur akustischen Signalisierung
   
### Passendes Gehäuse
- ein 3D druckbares Gehäuse wird [hier](./case_HB_Stamp_IO_EXT_LEDs_Buttons_FUEL4EP) bereitgestellt
- die gedruckten Gehäusebauteile werden so ineinander gesteckt:

- für das passgenaue Einlöten der LEDs bitte diese [Schablone](./case_HB_Stamp_IO_EXT_LEDs_Buttons_FUEL4EP/STL/LED_solder_helper.stl) verwenden 

### Hinweise
* bei der Nutzung des JLCPCB SMT Bestückungsservice ist darauf zu achten, dass **alle** benötigten SMD Bauteile als im Lager **verfügbar** angezeigt werden. Sonst bitte **NICHT** bestellen!

### KiCAD Plugin
- für die Erzeugung der JLCPCB Produktionsdaten wurde das Plugin [KiCAD JLCPCB tools](https://github.com/bouni/kicad-jlcpcb-tools) verwendet.

## benötigte Spezialbauteile zum Einlöten

- [Piezo Signalgeber](https://www.amazon.de/dp/B0C57D9RQ8)
- [6×6×8mm Taster mit aufsteckbaren farbigen Knopfkappen](https://www.amazon.de/Gebildet-Schalter-Momentane-Taktschalter-Drucktaster/dp/B082DBBPGC?th=1)

## Bestellen von Platinen

- die Platine kann direkt bei JLCPCB bestellt und dort auch assembliert werden
- die notwendigen Produktionsdaten stehen [hier](./jlcpcb/production_files/)
- ein Löten der SMD Bauteile per Hand ist möglich

## Disclaimer

-   die Nutzung der hier veröffentlichten Inhalte erfolgt vollständig auf eigenes Risiko und ohne jede Gewähr.

## Versionsverlauf

-   V1.0   18. Feb 2025: Initiale Vorabfreigabe
- 	KiCad Schaltplan-Editor   8.0.8-8.0.8-0~ubuntu22.04.1, release build unter Kubuntu22.04.1
- 	KiCad Leiterplatteneditor Version: 8.0.8-8.0.8-0~ubuntu22.04.1, release build unter Kubuntu22.04.1
- 	PCB Version 1.0
- 	Schematics  1.0

## Lizenz 

**Creative Commons BY-NC-SA**<br>
Give Credit, NonCommercial, ShareAlike

<br />This work is licensed under a <a rel="license" href="http://creativecommons.org/licenses/by-nc-sa/4.0/">Creative Commons Attribution-NonCommercial-ShareAlike 4.0 International License</a>.

-EOF

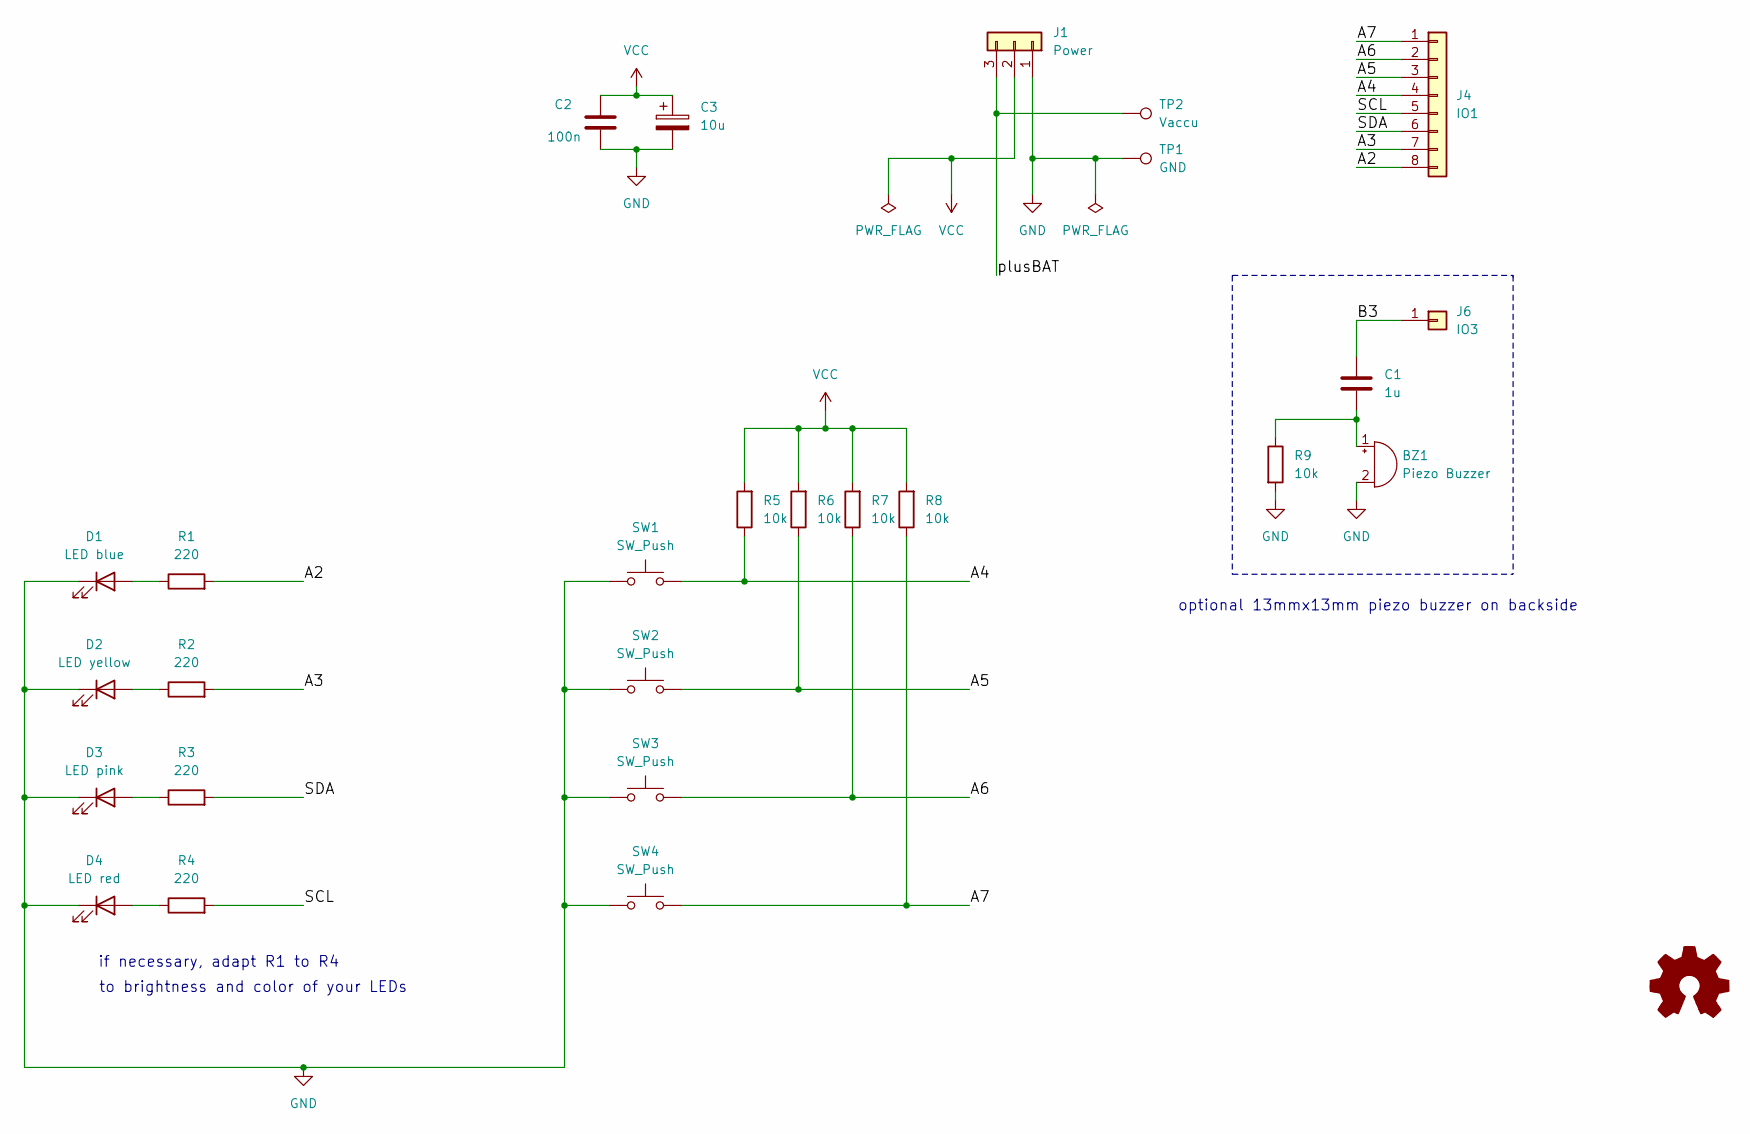
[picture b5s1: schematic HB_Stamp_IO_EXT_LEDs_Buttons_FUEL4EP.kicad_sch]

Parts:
BZ1: Piezo Buzzer; Buzzer_SMD_POPESQ_POPESQ_13mm_13mm_2.5mm
C1: 1u; C_0805_2012Metric_Pad1.18x1.45mm_HandSolder; LCSC C28323
C2: 100n; C_0805_2012Metric_Pad1.18x1.45mm_HandSolder; LCSC C28233
C3: 10u; C_0805_2012Metric_Pad1.18x1.45mm_HandSolder; LCSC C15850
D1: LED blue; LED_D3.0mm
D2: LED yellow; LED_D3.0mm
D3: LED pink; LED_D3.0mm
D4: LED red; LED_D3.0mm
J1: Power; PinHeader_1x03_P1.27mm_Vertical
J4: IO1; PinHeader_1x08_P1.27mm_Vertical
J6: IO3; PinHeader_1x01_P1.27mm_Vertical
LOGO1: Logo_Open_Hardware_Small; CC-BY-ND-SA_bottom
R1, R2, R3, R4: 220; R_0805_2012Metric_Pad1.20x1.40mm_HandSolder
R5, R6, R7, R8: 10k; R_0603_1608Metric_Pad0.98x0.95mm_HandSolder
R9: 10k; R_0805_2012Metric_Pad1.20x1.40mm_HandSolder
SW1, SW2, SW3, SW4: SW_Push; SW_PUSH_5.08mm
TP1: GND; TestPoint_Pad_1.0x1.0mm
TP2: Vaccu; TestPoint_Pad_1.0x1.0mm

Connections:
/A2: J4.8, R1.2
/A3: J4.7, R2.2
/A4: J4.4, R5.1, SW1.2
/A5: J4.3, R6.1, SW2.2
/A6: J4.2, R7.1, SW3.2
/A7: J4.1, R8.1, SW4.2
/B3: C1.1, J6.1
/SCL: J4.5, R4.2
/SDA: J4.6, R3.2
/plusBAT: J1.3, TP2.1
GND: BZ1.2 (-), C2.2, C3.2, D1.1 (K), D2.1 (K), D3.1 (K), D4.1 (K), J1.1, R9.2, SW1.1, SW2.1, SW3.1, SW4.1, TP1.1
unnamed: BZ1.1 (+), C1.2, R9.1
unnamed: D1.2 (A), R1.1
unnamed: D2.2 (A), R2.1
unnamed: D3.2 (A), R3.1
unnamed: D4.2 (A), R4.1
VCC: C2.1, C3.1, J1.2, R5.2, R6.2, R7.2, R8.2

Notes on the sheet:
to brightness and color of your LEDs
optional 13mmx13mm piezo buzzer on backside
if necessary, adapt R1 to R4

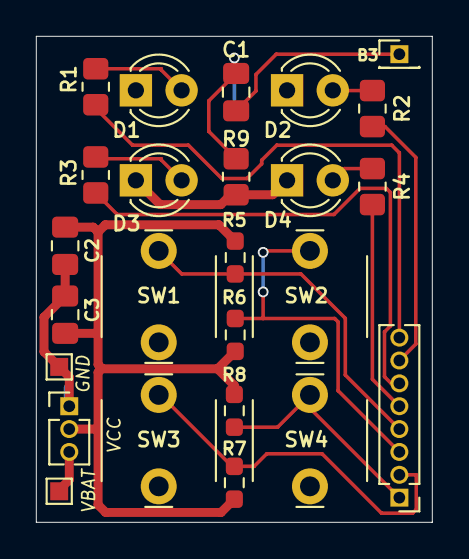
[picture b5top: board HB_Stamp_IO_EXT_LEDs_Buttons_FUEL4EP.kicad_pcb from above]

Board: 2 copper layers, 22.0 x 27.0 mm, 27 parts (1 on the bottom side), 17 nets.
